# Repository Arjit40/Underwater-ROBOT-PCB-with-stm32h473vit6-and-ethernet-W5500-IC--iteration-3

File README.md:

# Underwater-ROBOT-PCB-with-stm32h473vit6-and-ethernet-W5500-IC--iteration-3

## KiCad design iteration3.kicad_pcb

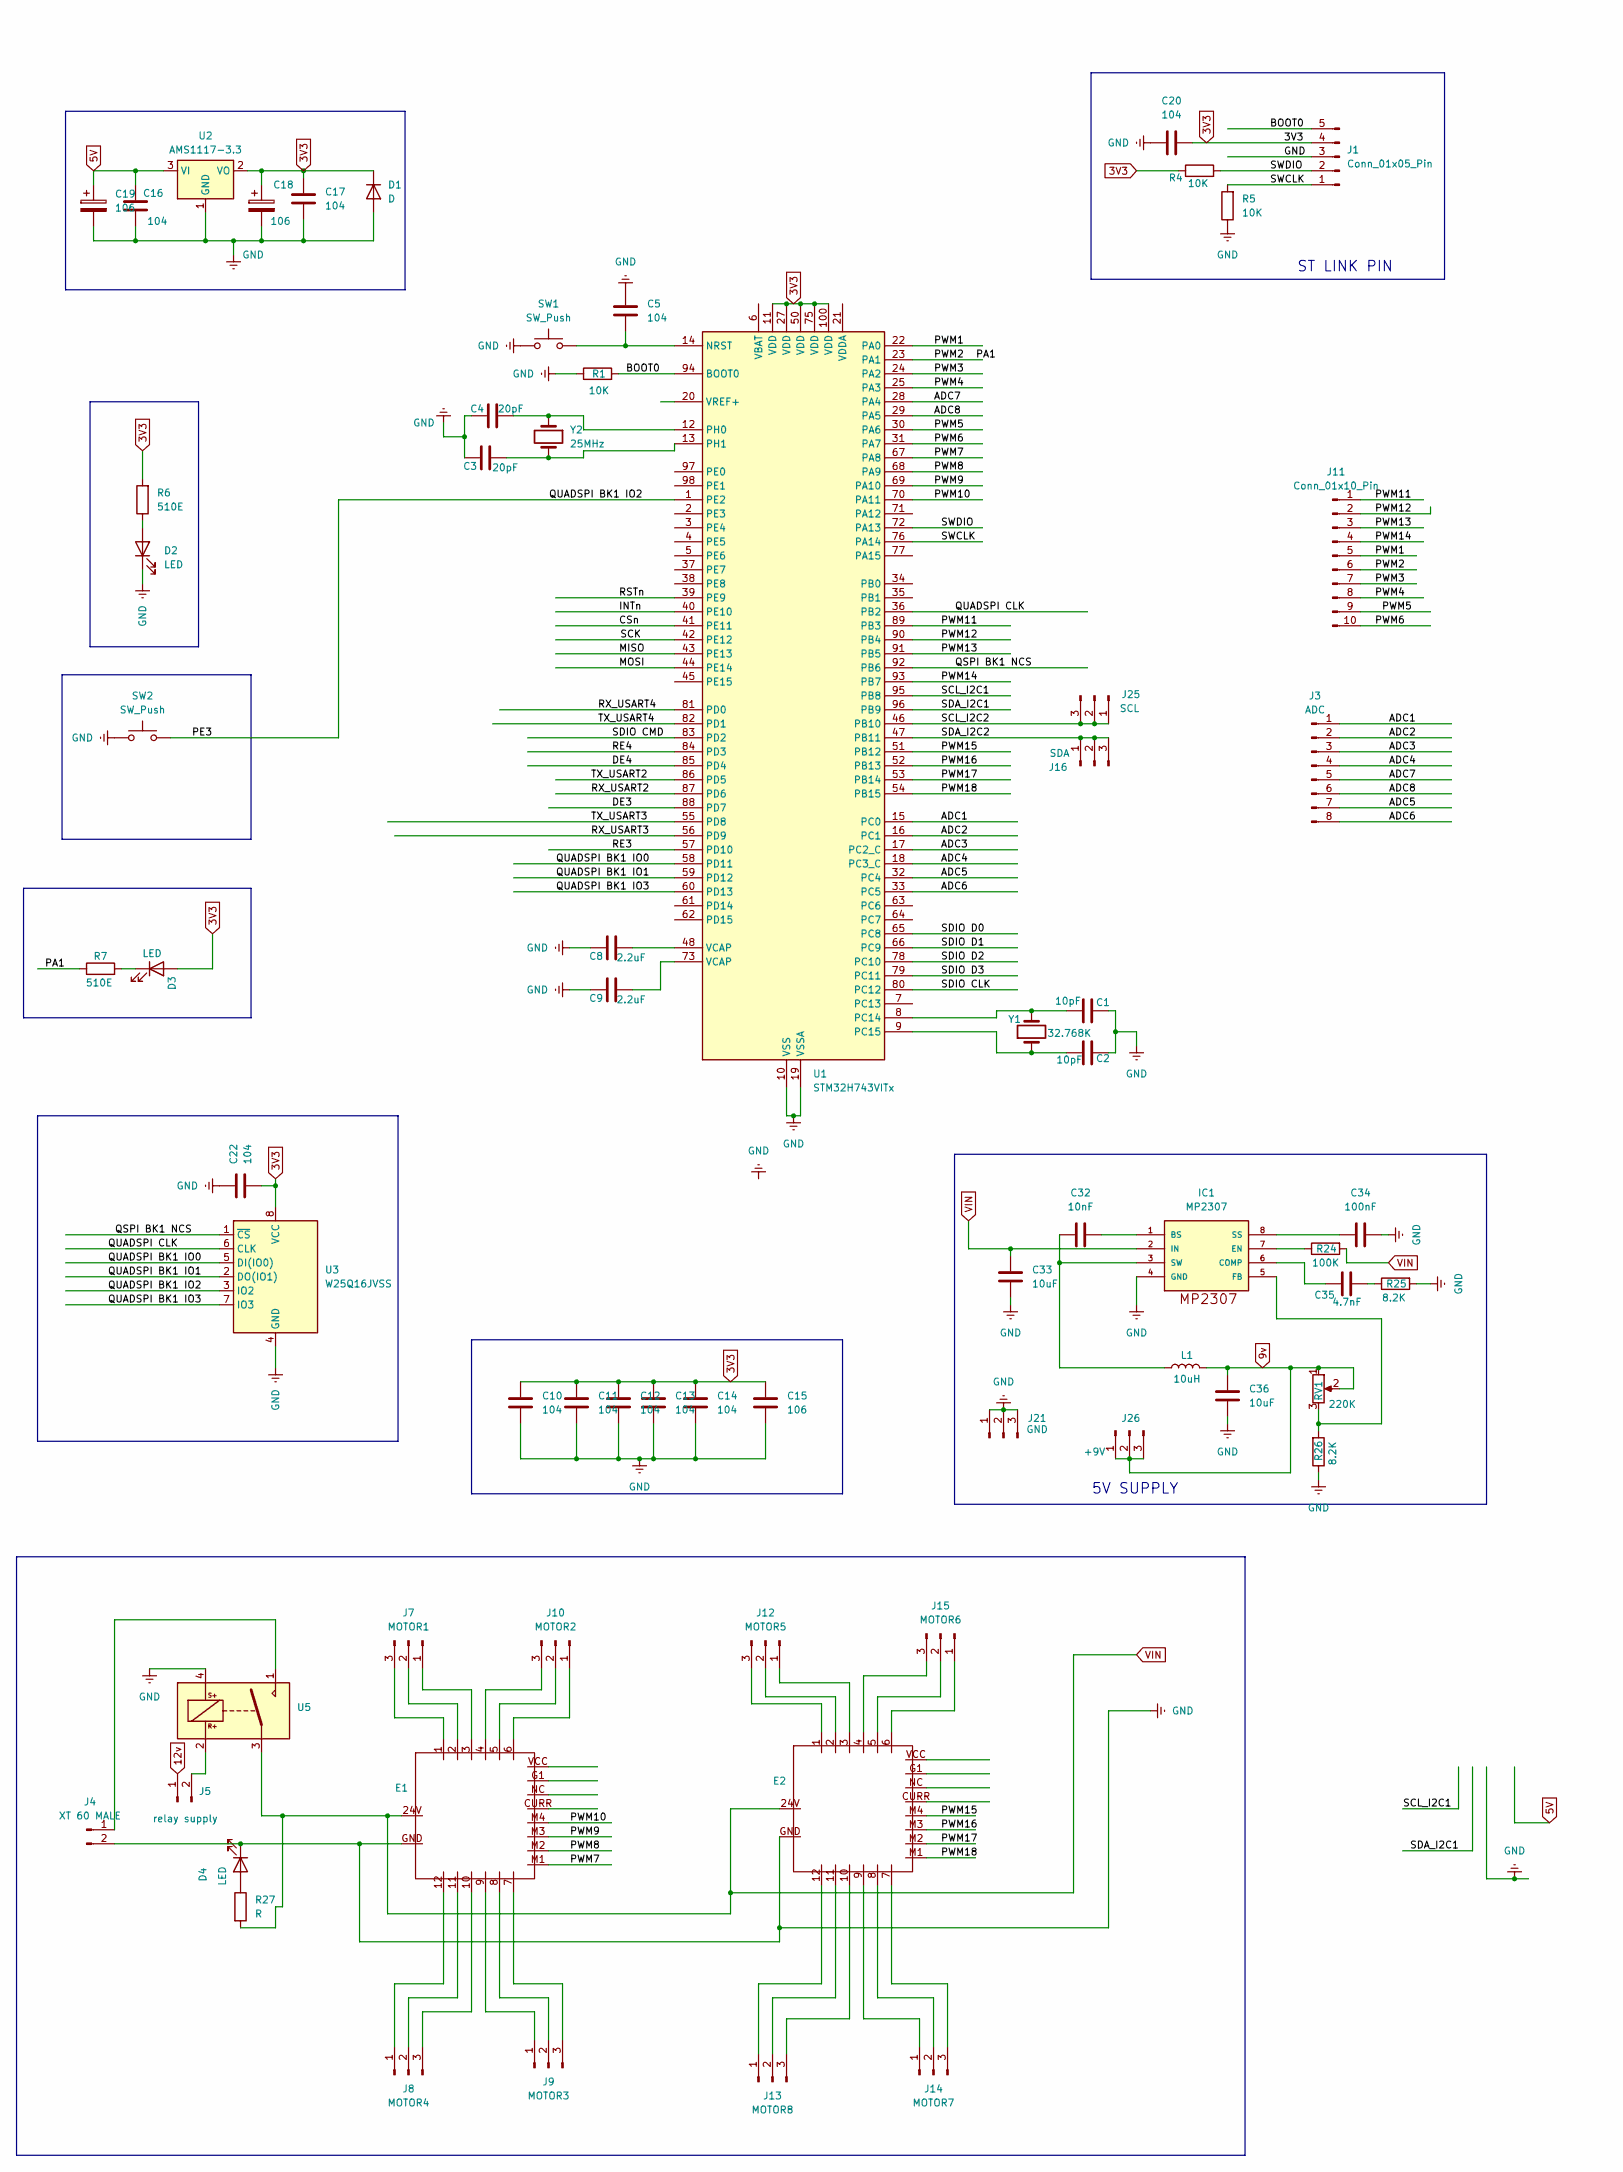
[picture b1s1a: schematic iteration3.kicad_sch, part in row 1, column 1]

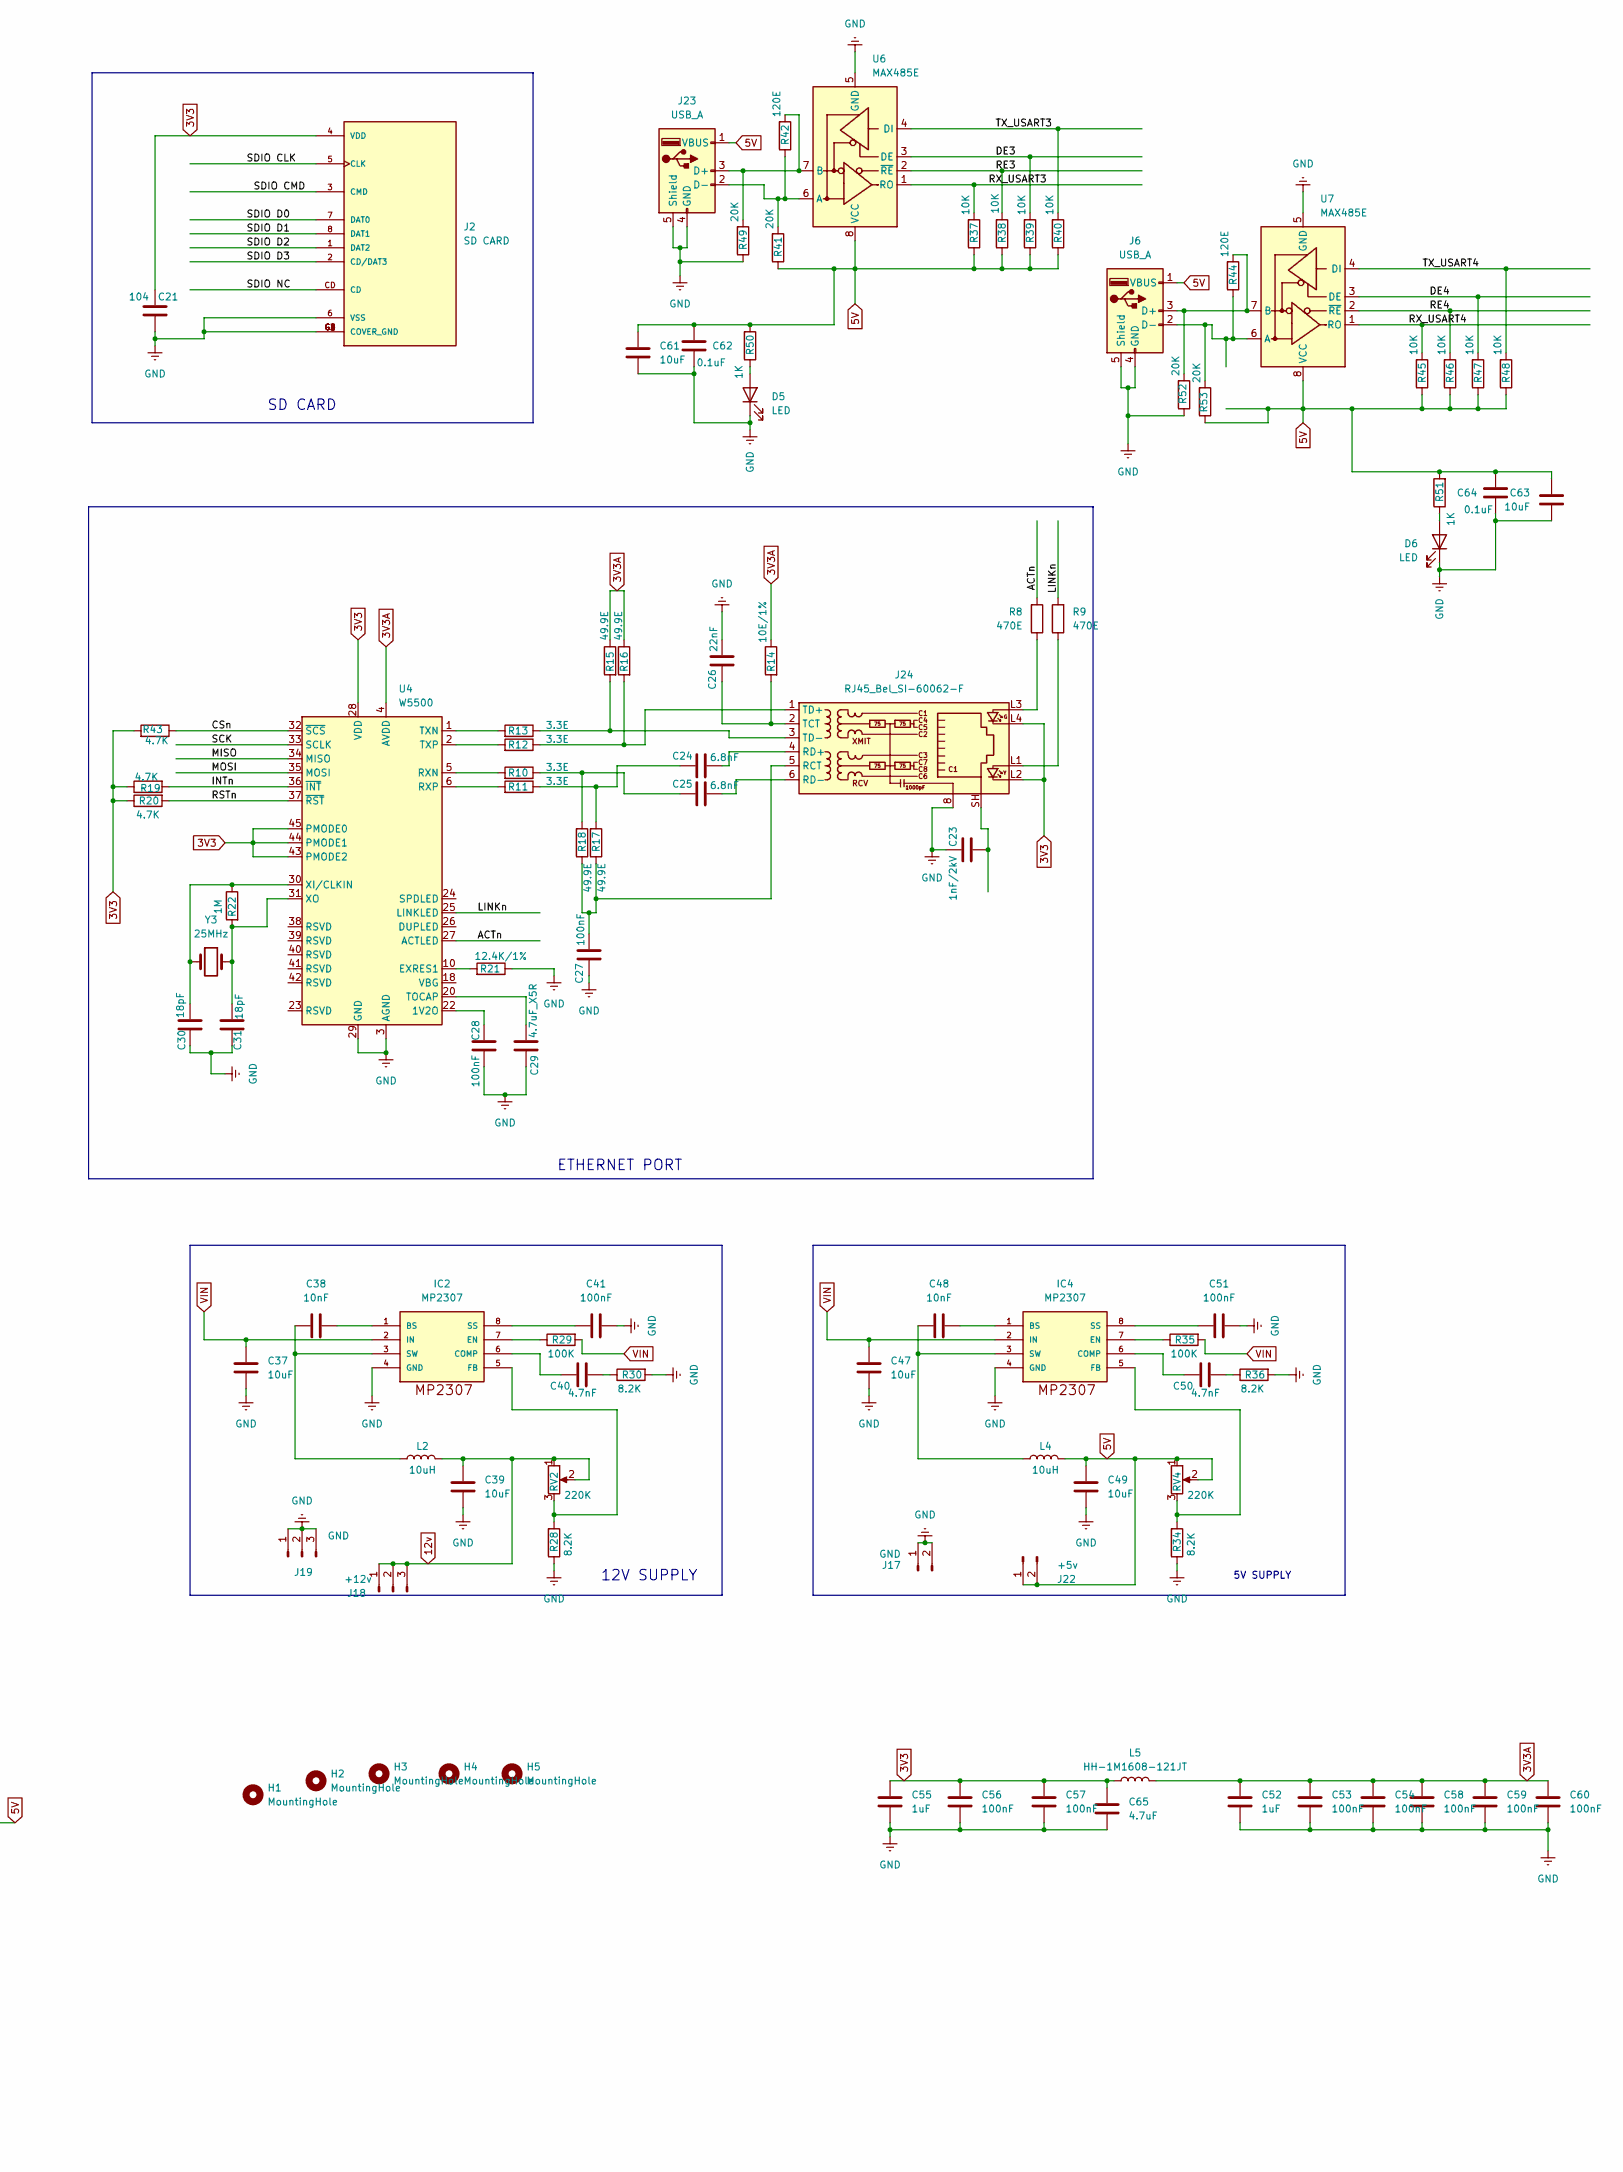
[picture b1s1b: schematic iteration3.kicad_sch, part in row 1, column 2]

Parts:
C1, C2: 10pF; C_0402_1005Metric
C3, C4: 20pF; C_0402_1005Metric
C5, C10, C11, C12, C13, C14, C16, C17, C20, C21, C22: 104; C_0402_1005Metric
C8, C9: 2.2uF; C_0603_1608Metric
C15, C18, C19: 106; C_0805_2012Metric
C23: 1nF/2kV; C_1812_4532Metric
C24, C25: 6.8nF; C_0402_1005Metric
C26: 22nF; C_0402_1005Metric
C27, C28, C34, C41, C51, C53, C54, C56, C57, C58, C59, C60: 100nF; C_0402_1005Metric
C29: 4.7uF_X5R; C_0402_1005Metric
C30, C31: 18pF; C_0402_1005Metric
C32, C38, C48: 10nF; C_0402_1005Metric
C33, C36, C37, C39, C47, C49, C61, C63: 10uF; C_1206_3216Metric
C35, C40, C50: 4.7nF; C_0402_1005Metric
C52, C55: 1uF; C_0402_1005Metric
C62, C64: 0.1uF; C_0402_1005Metric
C65: 4.7uF; C_0402_1005Metric
D1: D; D_SOD-323
D2, D3, D5, D6: LED; LED_0603_1608Metric
D4: LED; LED_1206_3216Metric_Pad1.42x1.75mm_HandSolder
E1, E2: Arduino_Mega2560_R3_2
H1, H2, H3, H4, H5: MountingHole; MountingHole_2.1mm
IC1, IC2, IC4: MP2307
J1: Conn_01x05_Pin; PinSocket_1x05_P2.54mm_Vertical
J2: SD CARD; PARTREV 1.0
J3: ADC; PinHeader_1x08_P2.54mm_Vertical
J4: XT 60 MALE; AMASS_XT60-F_1x02_P7.20mm_Vertical
J5: relay supply; TerminalBlock_Xinya_XY308-2.54-2P_1x02_P2.54mm_Horizontal
J6, J23: USB_A; USB_A_TE_292303-7_Horizontal
J7: MOTOR1; TerminalBlock_bornier-3_P5.08mm
J8: MOTOR4; TerminalBlock_bornier-3_P5.08mm
J9: MOTOR3; TerminalBlock_bornier-3_P5.08mm
J10: MOTOR2; TerminalBlock_bornier-3_P5.08mm
J11: Conn_01x10_Pin; PinHeader_1x10_P2.54mm_Vertical
J12: MOTOR5; TerminalBlock_bornier-3_P5.08mm
J13: MOTOR8; TerminalBlock_bornier-3_P5.08mm
J14: MOTOR7; TerminalBlock_bornier-3_P5.08mm
J15: MOTOR6; TerminalBlock_bornier-3_P5.08mm
J16: SDA; PinHeader_1x03_P2.54mm_Vertical
J17: GND; PinHeader_1x02_P2.54mm_Vertical
J18: +12v; PinHeader_1x03_P2.54mm_Vertical
J19, J21: GND; PinHeader_1x03_P2.54mm_Vertical
J22: +5v; PinHeader_1x02_P2.54mm_Vertical
J24: RJ45_Bel_SI-60062-F
J25: SCL; PinHeader_1x03_P2.54mm_Vertical
J26: +9V; PinHeader_1x03_P2.54mm_Vertical
L1, L2, L4: 10uH; L_Abracon_ASPI-0630LR
L5: HH-1M1608-121JT; L_TDK_MLZ1608
R1, R4, R5, R37, R38, R39, R40, R45, R46, R47, R48: 10K; R_0402_1005Metric
R6, R7: 510E; R_0402_1005Metric
R8, R9: 470E; R_0402_1005Metric
R10, R11, R12, R13: 3.3E; R_0402_1005Metric
R14: 10E/1%; R_0402_1005Metric
R15, R16, R17, R18: 49.9E; R_0402_1005Metric
R19, R20, R43: 4.7K; R_0402_1005Metric
R21: 12.4K/1%; R_0402_1005Metric
R22: 1M; R_0402_1005Metric
R24, R29, R35: 100K; R_0402_1005Metric
R25, R26, R28, R30, R34, R36: 8.2K; R_0402_1005Metric
R27: R; R_1206_3216Metric
R41, R49, R52, R53: 20K; R_0402_1005Metric
R42, R44: 120E; R_0402_1005Metric
R50, R51: 1K; R_0402_1005Metric
RV1, RV2, RV4: 220K; Potentiometer_ACP_CA6-VSMD_Vertical
SW1, SW2: SW_Push; SW_SPST_FSMSM
U1: STM32H743VITx; LQFP-100_14x14mm_P0.5mm
U2: AMS1117-3.3; SOT-223-3_TabPin2
U3: W25Q16JVSS; SOIC-8_5.23x5.23mm_P1.27mm
U4: W5500; LQFP-48_7x7mm_P0.5mm
U5: realy80A
U6, U7: MAX485E; SOIC-8_3.9x4.9mm_P1.27mm
Y1: 32.768K; Crystal_SMD_3215-2Pin_3.2x1.5mm
Y2, Y3: 25MHz; Crystal_SMD_5032-2Pin_5.0x3.2mm

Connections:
3V3: C10.1, C11.1, C12.1, C13.1, C14.1, C15.1, C17.1, C18.1, C20.2, C21.2, C22.2, C55.1, C56.1, C57.1, C65.1, D1.1 (K), D3.2 (A), J1.4, J2.4 (VDD), J24.L2, J24.L4, L5.1, R4.1, R6.2, R19.1, R20.1, R43.2, U1.11 (VDD), U1.27 (VDD), U1.50 (VDD), U1.75 (VDD), U1.100 (VDD), U2.2 (VO), U3.8 (VCC), U4.28 (VDD), U4.43 (PMODE2), U4.44 (PMODE1), U4.45 (PMODE0)
3V3A: C52.1, C53.1, C54.1, C58.1, C59.1, C60.1, L5.2, R14.1, R15.1, R16.1, U4.4 (AVDD), U4.8 (AVDD), U4.11 (AVDD), U4.15 (AVDD), U4.17 (AVDD), U4.21 (AVDD)
5V: C16.1, C19.1, C49.1, C61.2, C62.2, C63.2, C64.2, J6.1 (VBUS), J22.1, J22.2, J23.1 (VBUS), L4.2, R37.1, R38.1, R39.1, R40.1, R41.1, R45.1, R46.1, R47.1, R48.1, R50.2, R51.2, R53.1, RV4.1, RV4.2, U2.3 (VI), U6.8 (VCC), U7.8 (VCC)
9v: C36.1, J26.1, J26.2, J26.3, L1.2, RV1.1, RV1.2
12v: C39.1, J5.1, J18.1, J18.2, J18.3, L2.2, RV2.1, RV2.2
/ACTn: R8.2, U4.27 (ACTLED)
/ADC1: J3.1, U1.15 (PC0)
/ADC2: J3.2, U1.16 (PC1)
/ADC3: J3.3, U1.17 (PC2_C)
/ADC4: J3.4, U1.18 (PC3_C)
/ADC5: J3.7, U1.32 (PC4)
/ADC6: J3.8, U1.33 (PC5)
/ADC7: J3.5, U1.28 (PA4)
/ADC8: J3.6, U1.29 (PA5)
/BOOT0: J1.5, R1.2, U1.94 (BOOT0)
/CSn: R43.1, U1.41 (PE11), U4.32 (~SCS)
/DE3: R39.2, U1.88 (PD7), U6.3 (DE)
/DE4: R47.2, U1.85 (PD4), U7.3 (DE)
/INTn: R19.2, U1.40 (PE10), U4.36 (~INT)
/LINKn: R9.2, U4.25 (LINKLED)
/MISO: U1.43 (PE13), U4.34 (MISO)
/MOSI: U1.44 (PE14), U4.35 (MOSI)
/PA1: J11.6, R7.1, U1.23 (PA1)
/PE3: SW2.2, U1.1 (PE2), U3.3 (IO2)
/PWM1: J11.5, U1.22 (PA0)
/PWM3: J11.7, U1.24 (PA2)
/PWM4: J11.8, U1.25 (PA3)
/PWM5: J11.9, U1.30 (PA6)
/PWM6: J11.10, U1.31 (PA7)
/PWM7: E1.M1, U1.67 (PA8)
/PWM8: E1.M2, U1.68 (PA9)
/PWM9: E1.M3, U1.69 (PA10)
/PWM10: E1.M4, U1.70 (PA11)
/PWM11: J11.1, U1.89 (PB3)
/PWM12: J11.2, U1.90 (PB4)
/PWM13: J11.3, U1.91 (PB5)
/PWM14: J11.4, U1.93 (PB7)
/PWM15: E2.M4, U1.51 (PB12)
/PWM16: E2.M3, U1.52 (PB13)
/PWM17: E2.M2, U1.53 (PB14)
/PWM18: E2.M1, U1.54 (PB15)
/QSPI BK1 NCS: U1.92 (PB6), U3.1 (~CS)
/QUADSPI BK1 IO0: U1.58 (PD11), U3.5 (DI(IO0))
/QUADSPI BK1 IO1: U1.59 (PD12), U3.2 (DO(IO1))
/QUADSPI BK1 IO3: U1.60 (PD13), U3.7 (IO3)
/QUADSPI CLK: U1.36 (PB2), U3.6 (CLK)
/RE3: R38.2, U1.57 (PD10), U6.2 (~RE)
/RE4: R46.2, U1.84 (PD3), U7.2 (~RE)
/RSTn: R20.2, U1.39 (PE9), U4.37 (~RST)
/RX_USART2: U1.87 (PD6)
/RX_USART3: R37.2, U1.56 (PD9), U6.1 (RO)
/RX_USART4: R45.2, U1.81 (PD0), U7.1 (RO)
/SCK: U1.42 (PE12), U4.33 (SCLK)
/SCL_I2C1: U1.95 (PB8)
/SCL_I2C2: J25.1, J25.2, J25.3, U1.46 (PB10)
/SDA_I2C1: U1.96 (PB9)
/SDA_I2C2: J16.1, J16.2, J16.3, U1.47 (PB11)
/SDIO CLK: J2.5 (CLK), U1.80 (PC12)
/SDIO CMD: J2.3 (CMD), U1.83 (PD2)
/SDIO D0: J2.7 (DAT0), U1.65 (PC8)
/SDIO D1: J2.8 (DAT1), U1.66 (PC9)
/SDIO D2: J2.1 (DAT2), U1.78 (PC10)
/SDIO D3: J2.2 (CD/DAT3), U1.79 (PC11)
/SWCLK: J1.1, R5.2, U1.76 (PA14)
/SWDIO: J1.2, R4.2, U1.72 (PA13)
/TX_USART2: U1.86 (PD5)
/TX_USART3: R40.2, U1.55 (PD8), U6.4 (DI)
/TX_USART4: R48.2, U1.82 (PD1), U7.4 (DI)
GND: C1.2, C2.2, C3.2, C4.2, C5.1, C8.2, C9.2, C10.2, C11.2, C12.2, C13.2, C14.2, C15.2, C16.2, C17.2, C18.2, C19.2, C20.1, C21.1, C22.1, C23.2, C26.1, C27.2, C28.1, C29.1, C30.2, C31.2, C33.2, C34.2, C36.2, C37.2, C39.2, C41.2, C47.2, C49.2, C51.2, C52.2, C53.2, C54.2, C55.2, C56.2, C57.2, C58.2, C59.2, C60.2, C61.1, C62.1, C63.1, C64.1, C65.2, D1.2 (A), D2.1 (K), D4.1 (K), D5.1 (K), D6.1 (K), E1.GND, E2.GND, IC1.4 (GND), IC2.4 (GND), IC4.4 (GND), J1.3, J2.6 (VSS), J2.G1 (COVER_GND), J2.G2 (COVER_GND), J2.G3 (COVER_GND), J2.G4 (COVER_GND), J4.2, J6.4 (GND), J6.5 (Shield), J17.1, J17.2, J19.1, J19.2, J19.3, J21.1, J21.2, J21.3, J23.4 (GND), J23.5 (Shield), J24.8, R1.1, R5.1, R21.1, R25.2, R26.1, R28.1, R30.2, R34.1, R36.2, R49.1, R52.1, SW1.1, SW2.1, U1.10 (VSS), U1.19 (VSSA), U1.26 (VSS), U1.49 (VSS), U1.74 (VSS), U1.99 (VSS), U2.1 (GND), U3.4 (GND), U4.3 (AGND), U4.9 (AGND), U4.14 (AGND), U4.16 (AGND), U4.19 (AGND), U4.29 (GND), U4.48 (AGND), U5.4, U6.5 (GND), U7.5 (GND)
unnamed: C8.1, U1.48 (VCAP)
unnamed: C9.1, U1.73 (VCAP)
unnamed: C23.1, J24.SH
unnamed: C24.2, R11.1, R17.2
unnamed: C25.2, R10.1, R18.2
unnamed: C35.2, R25.1
unnamed: C40.2, R30.1
unnamed: C50.2, R36.1
unnamed: D2.2 (A), R6.1
unnamed: D3.1 (K), R7.2
unnamed: D4.2 (A), R27.1
unnamed: D5.2 (A), R50.1
unnamed: D6.2 (A), R51.1
unnamed: C32.2, IC1.1 (BS)
unnamed: C35.1, IC1.6 (COMP)
unnamed: IC1.7 (EN), R24.1
unnamed: IC1.5 (FB), R26.2, RV1.3
unnamed: C34.1, IC1.8 (SS)
unnamed: C32.1, IC1.3 (SW), L1.1
unnamed: C38.2, IC2.1 (BS)
unnamed: C40.1, IC2.6 (COMP)
unnamed: IC2.7 (EN), R29.1
unnamed: IC2.5 (FB), R28.2, RV2.3
unnamed: C41.1, IC2.8 (SS)
unnamed: C38.1, IC2.3 (SW), L2.1
unnamed: C48.2, IC4.1 (BS)
unnamed: C50.1, IC4.6 (COMP)
unnamed: IC4.7 (EN), R35.1
unnamed: IC4.5 (FB), R34.2, RV4.3
unnamed: C51.1, IC4.8 (SS)
unnamed: C48.1, IC4.3 (SW), L4.1
unnamed: J4.1, U5.1
unnamed: J5.2, U5.2
unnamed: J6.3 (D+), R44.2, R52.2, U7.7 (B)
unnamed: J6.2 (D-), R44.1, R53.2, U7.6 (A)
unnamed: E1.3, J7.1
unnamed: E1.2, J7.2
unnamed: E1.1, J7.3
unnamed: E1.12, J8.1
unnamed: E1.11, J8.2
unnamed: E1.10, J8.3
unnamed: E1.9, J9.1
unnamed: E1.8, J9.2
unnamed: E1.7, J9.3
unnamed: E1.6, J10.1
unnamed: E1.5, J10.2
unnamed: E1.4, J10.3
unnamed: E2.3, J12.1
unnamed: E2.2, J12.2
unnamed: E2.1, J12.3
unnamed: E2.12, J13.1
unnamed: E2.11, J13.2
unnamed: E2.10, J13.3
unnamed: E2.9, J14.1
unnamed: E2.8, J14.2
unnamed: E2.7, J14.3
unnamed: E2.6, J15.1
unnamed: E2.5, J15.2
unnamed: E2.4, J15.3
unnamed: J23.3 (D+), R42.2, R49.2, U6.7 (B)
unnamed: J23.2 (D-), R41.2, R42.1, U6.6 (A)
unnamed: J24.L1, R9.1
unnamed: J24.L3, R8.1
unnamed: C27.1, J24.5 (RCT), R17.1, R18.1
unnamed: C24.1, J24.4 (RD+)
unnamed: C25.1, J24.6 (RD-)
unnamed: C26.2, J24.2 (TCT), R14.2
unnamed: J24.1 (TD+), R12.1, R16.2
unnamed: J24.3 (TD-), R13.1, R15.2
unnamed: C5.2, SW1.2, U1.14 (NRST)
unnamed: C1.1, U1.8 (PC14), Y1.2
unnamed: C2.1, U1.9 (PC15), Y1.1
unnamed: C4.1, U1.12 (PH0), Y2.1
unnamed: C3.1, U1.13 (PH1), Y2.2
unnamed: C28.2, U4.22 (1V2O)
unnamed: R21.2, U4.10 (EXRES1)
unnamed: R10.2, U4.5 (RXN)
unnamed: R11.2, U4.6 (RXP)
unnamed: C29.2, U4.20 (TOCAP)
unnamed: R13.2, U4.1 (TXN)
unnamed: R12.2, U4.2 (TXP)
unnamed: C30.1, R22.1, U4.30 (XI/CLKIN), Y3.1
unnamed: C31.1, R22.2, U4.31 (XO), Y3.2
VIN: C33.1, C37.1, C47.1, E1.24V, E2.24V, IC1.2 (IN), IC2.2 (IN), IC4.2 (IN), R24.2, R27.2, R29.2, R35.2, U5.3

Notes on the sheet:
12V SUPPLY
5V SUPPLY
ETHERNET PORT
ST LINK PIN
5V SUPPLY
SD CARD

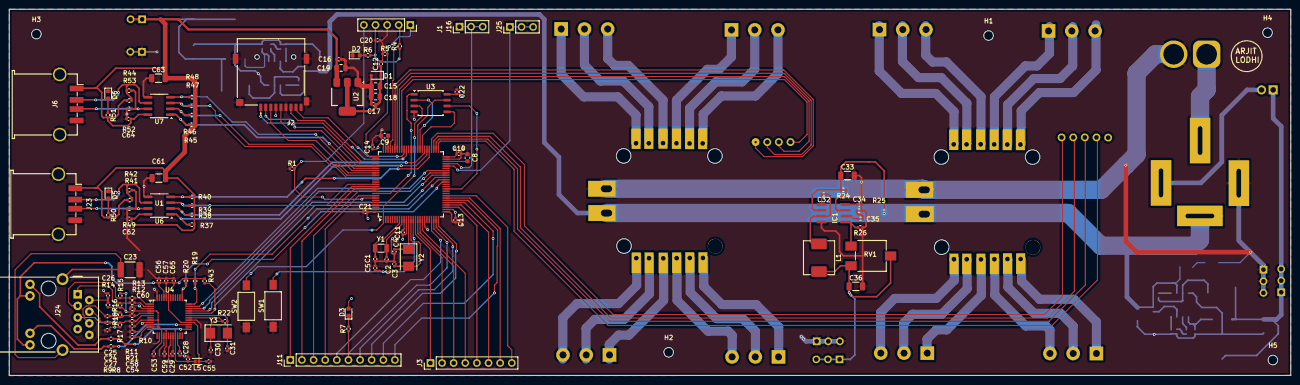
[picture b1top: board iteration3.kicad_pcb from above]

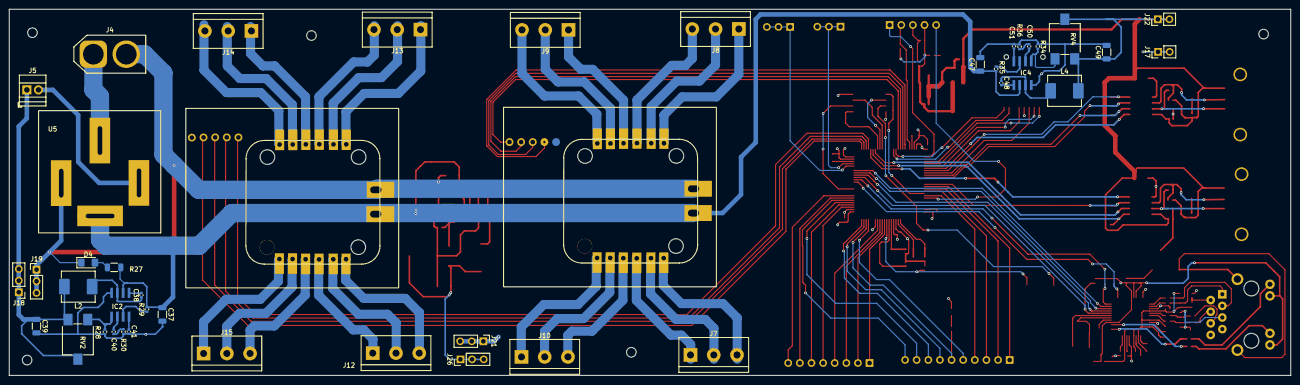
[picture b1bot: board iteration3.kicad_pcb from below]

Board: 4 copper layers, 280.0 x 80.0 mm, 165 parts (43 on the bottom side), 149 nets.
